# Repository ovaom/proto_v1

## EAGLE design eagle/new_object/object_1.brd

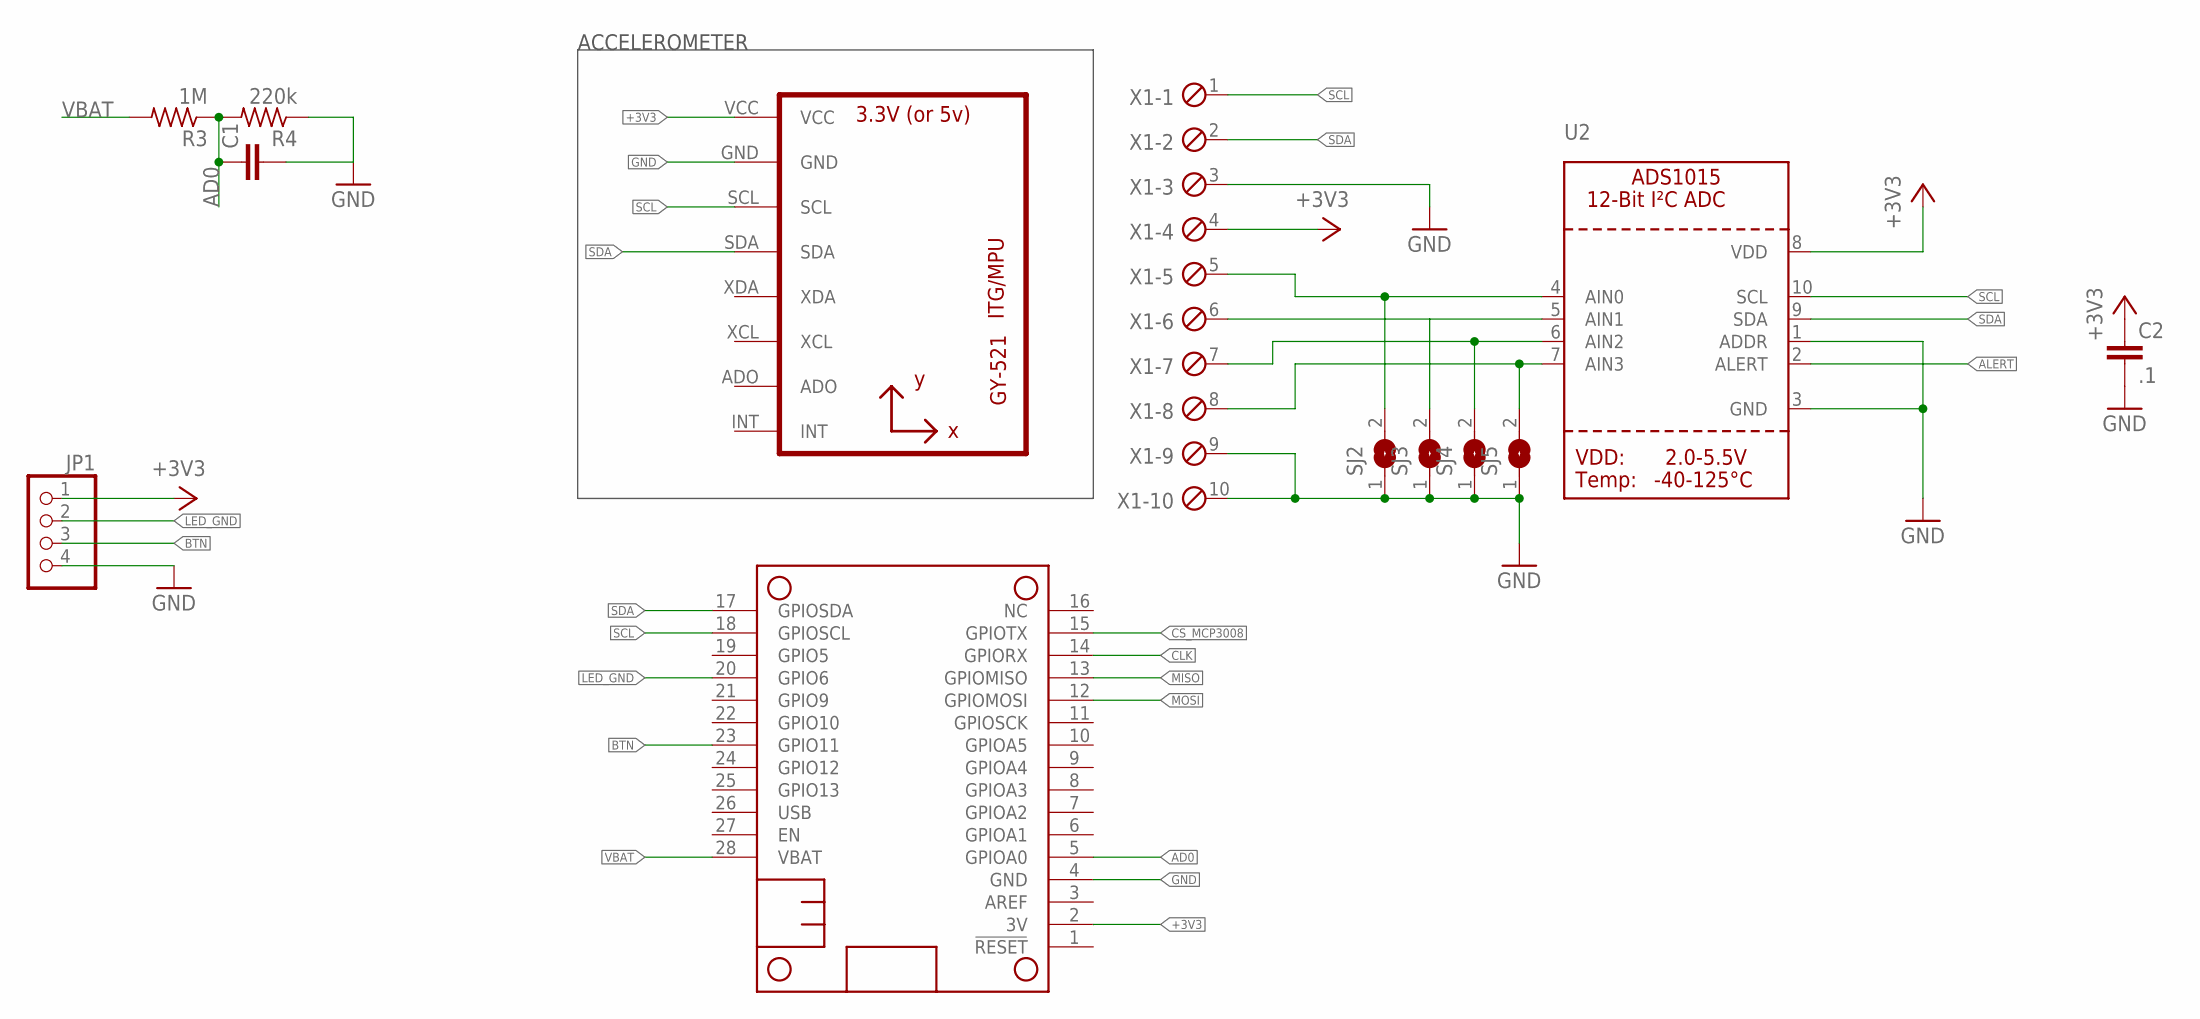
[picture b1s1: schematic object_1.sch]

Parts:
C1: C-EUC0805K; C0805K
C2: .1; C0805K
JP1: PINHD-1X4/90; 1X04/90
MS1: FEATHERWING_NODIM; FEATHERWING_DIM
R3: 1M; M0805
R4: 220k; M0805
SJ2, SJ3, SJ4, SJ5: SOLDERJUMPER; SOLDERJUMPER_ARROW_NOPASTE
U1: GY-521MPU6050; GY-521
U2: ADC_ADS1015; MSOP10
X1: MPT10; 10POL254

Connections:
+3V3: C2.1, JP1.1, MS1.2 (3V), U1.VCC, U2.8 (VDD), X1.4
AD0: C1.1, MS1.5 (GPIOA0), R3.1, R4.2
ALERT: U2.2 (ALERT)
BTN: JP1.3, MS1.23 (GPIO11)
CLK: MS1.14 (GPIORX)
CS_MCP3008: MS1.15 (GPIOTX)
GND: C1.2, C2.2, JP1.4, MS1.4 (GND), R4.1, SJ2.1, SJ3.1, SJ4.1, SJ5.1, U1.GND, U2.1 (ADDR), U2.3 (GND), X1.3, X1.9, X1.10
LED_GND: JP1.2, MS1.20 (GPIO6)
MISO: MS1.13 (GPIOMISO)
MOSI: MS1.12 (GPIOMOSI)
unnamed: SJ2.2, U2.4 (AIN0), X1.5
unnamed: SJ3.2, U2.5 (AIN1), X1.6
unnamed: SJ4.2, U2.6 (AIN2), X1.7
unnamed: SJ5.2, U2.7 (AIN3), X1.8
SCL: MS1.18 (GPIOSCL), U1.SCL, U2.10 (SCL), X1.1
SDA: MS1.17 (GPIOSDA), U1.SDA, U2.9 (SDA), X1.2
VBAT: MS1.28 (VBAT), R3.2

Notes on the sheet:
ACCELEROMETER

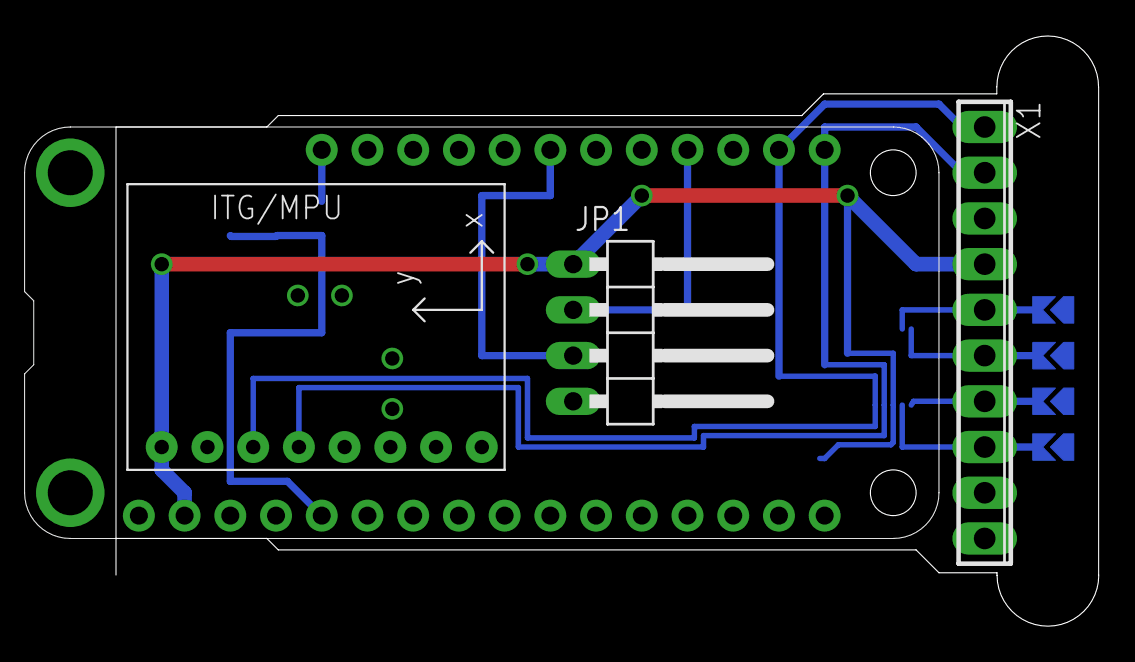
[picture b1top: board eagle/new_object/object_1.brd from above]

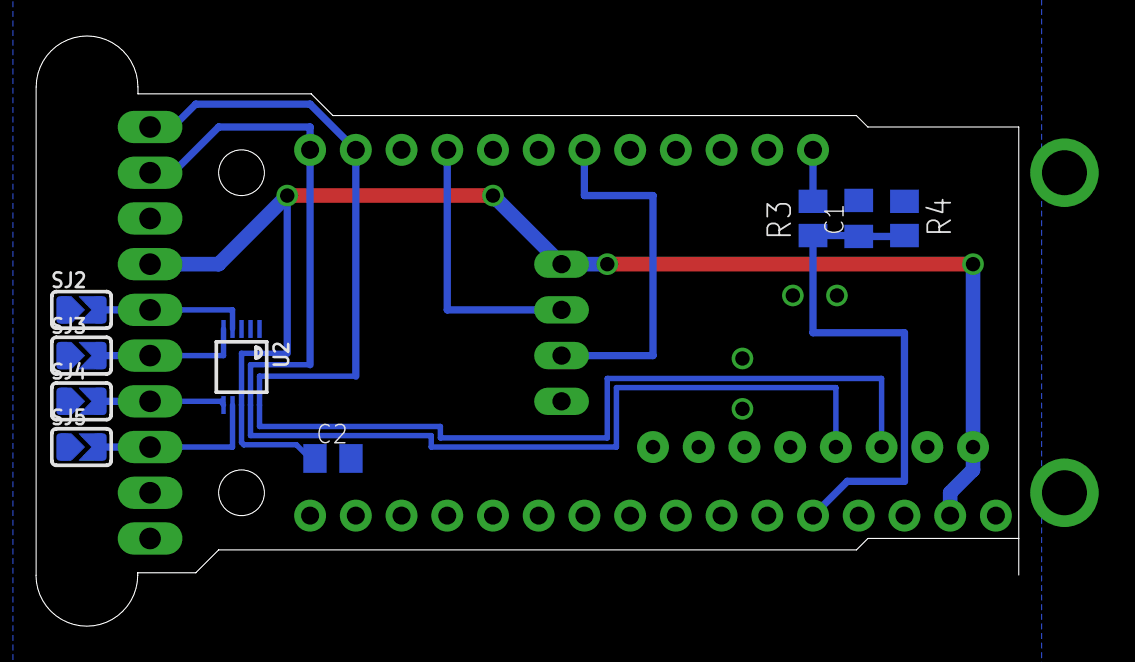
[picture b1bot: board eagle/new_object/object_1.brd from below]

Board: 2 copper layers, 54.6 x 32.8 mm, 13 parts (9 on the bottom side), 12 nets.

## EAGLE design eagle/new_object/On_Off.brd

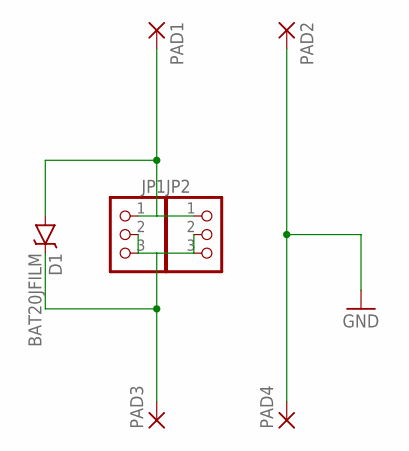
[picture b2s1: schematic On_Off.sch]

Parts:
D1: BAT20JFILM; SOD-323
JP1, JP2: PINHD-1X3; 1X03
PAD1, PAD2, PAD3, PAD4: SMD5; SMD2,54-5,08

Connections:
BATTERY: D1.C, JP1.2, JP1.3, JP2.2, JP2.3, PAD3.1
FEATHER: D1.A, JP1.1, JP2.1, PAD1.1
GND: PAD2.1, PAD4.1

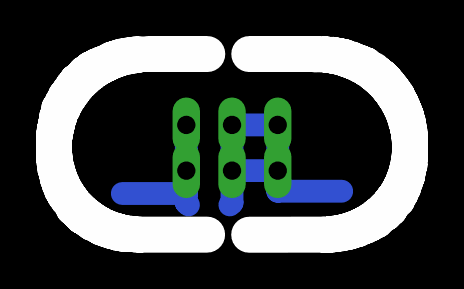
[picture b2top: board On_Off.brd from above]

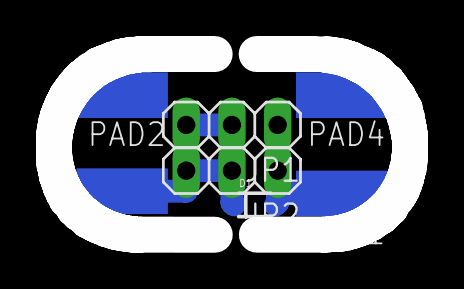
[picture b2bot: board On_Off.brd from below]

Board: 2 copper layers, 19.8 x 10.0 mm, 7 parts (7 on the bottom side), 3 nets.

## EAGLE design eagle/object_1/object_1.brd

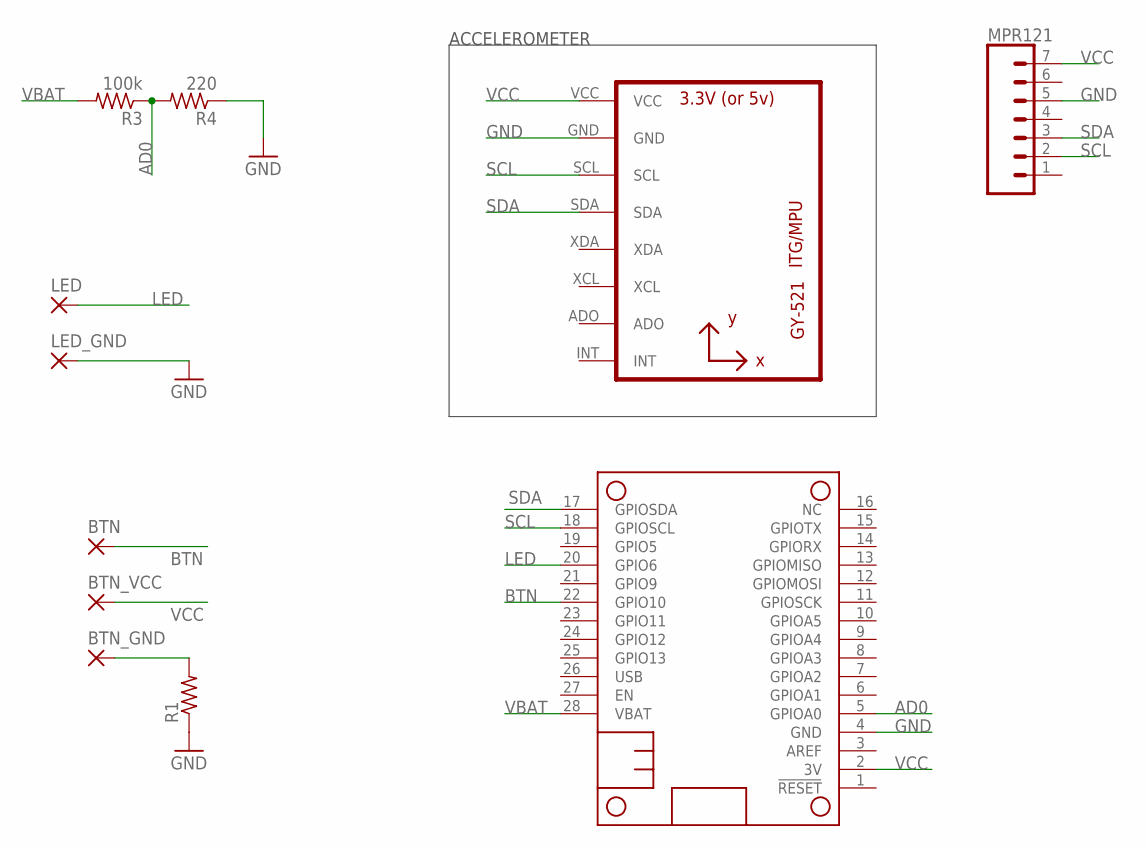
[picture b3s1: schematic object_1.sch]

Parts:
BTN: 2,15/1,0
BTN_GND: 2,15/1,0
BTN_VCC: 2,15/1,0
LED: 2,15/1,0
LED_GND: 2,15/1,0
MPR121: CONN_07NO_SILK; 1X07_NO_SILK
MS1: FEATHERWING
R1: 0204/5
R3: 100k; 0204/5
R4: 220; 0204/5
U1: GY-521MPU6050; GY-521

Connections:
AD0: MS1.5 (GPIOA0), R3.1, R4.2
BTN: BTN.1, MS1.22 (GPIO10)
GND: LED_GND.1, MPR121.5, MS1.4 (GND), R1.1, R4.1, U1.GND
GND_BTN: BTN_GND.1, R1.2
LED: LED.1, MS1.20 (GPIO6)
SCL: MPR121.2, MS1.18 (GPIOSCL), U1.SCL
SDA: MPR121.3, MS1.17 (GPIOSDA), U1.SDA
VBAT: MS1.28 (VBAT), R3.2
VCC: BTN_VCC.1, MPR121.7, MS1.2 (3V), U1.VCC

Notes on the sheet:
ACCELEROMETER

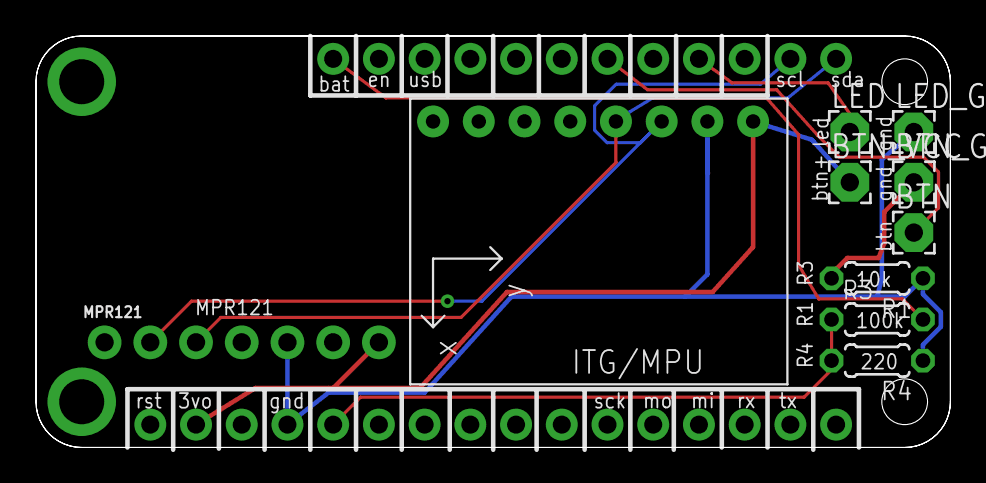
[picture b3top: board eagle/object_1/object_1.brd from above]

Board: 2 copper layers, 50.8 x 22.9 mm, 11 parts (0 on the bottom side), 9 nets.

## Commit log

2018-10-09 Create LICENSE
2018-10-09 Opening sources
2018-10-09 remove ds_store and server
2018-10-09 Add server files
2018-10-18 add eagle files for object_0 and object_1
2018-10-18 add gitignore
2018-10-18 remove DS_store
2018-11-07 Design a more universal PCB with ADS1015 and GY521
2018-11-07 Add a simple HW test sketch for debug
2018-11-07 Change the PCB design a little for easier 3d printing
2018-11-07 Add ADC readings to HW test sketch
2018-11-21 Change switch to pin 23, clean the mess git did with the files

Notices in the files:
parts and their libraries:
SparkFun-DiscreteSemi: Licensing: Creative Commons ShareAlike 4.0 International - https://creativecommons.org/licenses/by-sa/4.0
